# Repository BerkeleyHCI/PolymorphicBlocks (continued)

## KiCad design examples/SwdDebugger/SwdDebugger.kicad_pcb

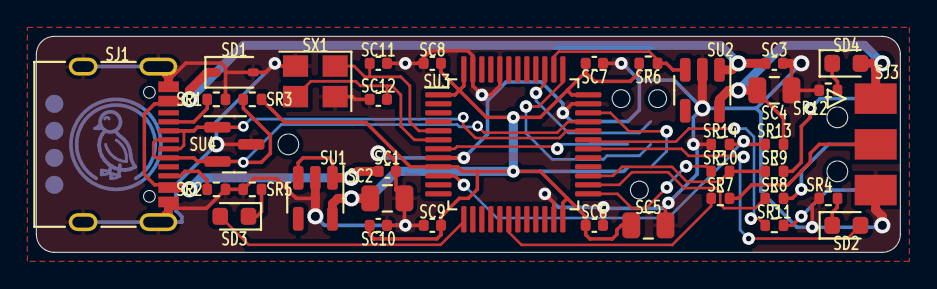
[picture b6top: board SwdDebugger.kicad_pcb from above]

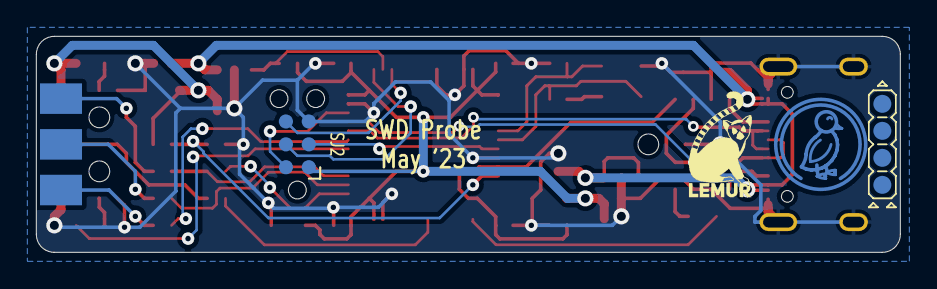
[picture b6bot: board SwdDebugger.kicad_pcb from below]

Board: 2 copper layers, 48.0 x 12.0 mm, 44 parts (4 on the bottom side), 30 nets.

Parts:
SC1, SC3, SC6, SC7, SC8, SC9, SC10, SC11, SC12: C_0402_1005Metric
SC2, SC4, SC5: C_0805_2012Metric
SD1: BZT52-B5V6S_R1_00001 (PANJIT International) - 100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; D_SOD-323
SD2, SD4: LED_0603_1608Metric
SD3: C2290 (Hubei KENTO Elec) - White 0603 Light Emitt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; LED_0603_1608Metric
SH1, SH2, SH3: JlcToolingHole_1.152mm
SJ1: COM-15111 (Sparkfun); USB_C_Receptacle_XKB_U262-16XN-4BVC11
SJ2: Tag-Connect_TC2030-IDC-NL_2x03_P1.27mm_Vertical
SJ3: PinHeader2.54 Shrouded 2x3 (Generic); PinHeader_2x03_P2.54mm_EdgeInline
SR1, SR2, SR3, SR4, SR5, SR6, SR7, SR8, SR9, SR10, SR11, SR12, SR13, SR14: R_0402_1005Metric
SU1, SU2: AP2204K-3.3 (Diodes Incorporated); SOT-23-5
SU3: STM32F103xxT6 (STMicroelectronics); LQFP-48_7x7mm_P0.5mm
SU4: PESD5V0X1BT (Nexperia); SOT-23
SX1: Crystal_SMD_3225-4Pin_3.2x2.5mm
UU4: Duck; Symbol_Duckling
UU5: Lemur; Symbol_LemurSmall
UU6: IdDots4; Indicator_IdDots_4

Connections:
en_pull.io: SR6.2, SU2.3, SU3.38
gnd: SC1.2, SC2.2, SC3.2, SC4.2, SC5.2, SC6.2, SC7.2, SC8.2, SC9.2, SC10.2, SC11.2, SC12.2, SD1.2, SJ1.A1, SJ1.A12, SJ1.B1, SJ1.B12, SJ1.S1, SJ2.5, SJ3.5, SR1.1, SR2.1, SR4.2, SR5.2, SR12.2, SR14.2, SU1.2, SU2.2, SU3.8, SU3.23, SU3.35, SU3.44, SU3.47, SU4.3, SX1.2, SX1.4
led_target.res.a: SD4.1, SR12.1
led_tgt.res.a: SD2.1, SR4.1
led_tgt.signal: SD2.2, SU3.30
led_usb.res.a: SD3.1, SR5.1
led_usb.signal: SD3.2, SU3.13
mcu.swd.swo: SJ2.6, SU3.39
mcu.swd_node.reset: SJ2.3, SU3.7
mcu.swd_node.swclk: SJ2.4, SU3.37
mcu.swd_node.swdio: SJ2.2, SU3.34
mcu.xtal_node.driver.xtal_in: SC11.1, SU3.5, SX1.1
mcu.xtal_node.driver.xtal_out: SC12.1, SU3.6, SX1.3
target_drv.reset_in: SR7.1, SU3.18
target_drv.swclk_in: SR8.1, SU3.26
target_drv.swd.reset: SJ3.3, SR7.2
target_drv.swd.swclk: SJ3.4, SR8.2
target_drv.swd.swdio: SJ3.2, SR9.2
target_drv.swdio_in: SR10.1, SU3.25
target_drv.swdio_out: SR9.1, SR10.2, SU3.27
target_drv.swo_in: SJ3.6, SR11.2
target_drv.swo_out: SR11.1, SU3.31
target_sense.output: SR13.2, SR14.1, SU3.10
usb.conn.A5: SJ1.A5, SR1.2
usb.conn.B5: SJ1.B5, SR2.2
usb_chain_0.d_N: SJ1.A7, SJ1.B7, SU3.32, SU4.1
usb_chain_0.d_P: SJ1.A6, SJ1.B6, SR3.2, SU3.33, SU4.2
v3v3: SC2.1, SC5.1, SC6.1, SC7.1, SC8.1, SC9.1, SC10.1, SJ2.1, SR3.1, SR6.1, SU1.5, SU3.1, SU3.9, SU3.24, SU3.36, SU3.48
vtarget: SC4.1, SD4.2, SJ3.1, SR13.1, SU2.5
vusb: SC1.1, SC3.1, SD1.1, SJ1.A4, SJ1.A9, SJ1.B4, SJ1.B9, SU1.1, SU1.3, SU2.1

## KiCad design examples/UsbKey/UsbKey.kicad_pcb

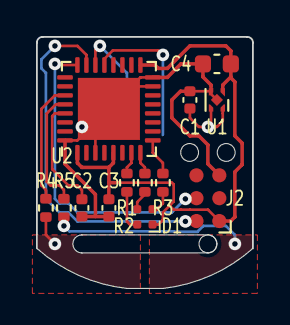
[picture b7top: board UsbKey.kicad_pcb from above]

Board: 2 copper layers, 12.0 x 14.0 mm, 14 parts (1 on the bottom side), 16 nets.

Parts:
C1, C2, C3: C_0402_1005Metric
C4: C_0603_1608Metric
D1: FC-B1010RGBT-HG (Foshan NationStar Optoelectronic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; LED_Lumex_SML-LX0404SIUPGUSB
J1: USB A pads; USB_A_Pads
J2: Tag-Connect_TC2030-IDC-NL_2x03_P1.27mm_Vertical
R1, R2, R3, R4, R5: R_0402_1005Metric
U1: LP5907SNX-3.3/NOPB (Texas Instruments); UDFN-4-1EP_1x1mm_P0.65mm_EP0.48x0.48mm
U2: STM32L432Kxxx (STMicroelectronics); QFN-32-1EP_5x5mm_P0.5mm_EP3.45x3.45mm

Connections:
gnd: C1.2, C2.2, C3.2, C4.2, J1.4, J2.5, U1.2, U1.5, U2.3, U2.15, U2.16, U2.32, U2.33
mcu.swd_node.swclk: J2.4, U2.24
mcu.swd_node.swdio: J2.2, U2.23
rgb.blue_res.a: D1.4, R3.1
rgb.green_res.a: D1.3, R2.1
rgb.red_res.a: D1.2, R1.1
rgb.signals.blue: R3.2, U2.9
rgb.signals.green: R2.2, U2.8
rgb.signals.red: R1.2, U2.7
ts1.io: R4.1, U2.27
ts2.io: R5.1, U2.28
tss.io: C2.1, U2.29
usb.pwr: C1.1, J1.1, U1.3, U1.4
usb.usb.dm: J1.2, U2.21
usb.usb.dp: J1.3, U2.22
v3v3: C3.1, C4.1, D1.1, J2.1, U1.1, U2.1, U2.5, U2.17

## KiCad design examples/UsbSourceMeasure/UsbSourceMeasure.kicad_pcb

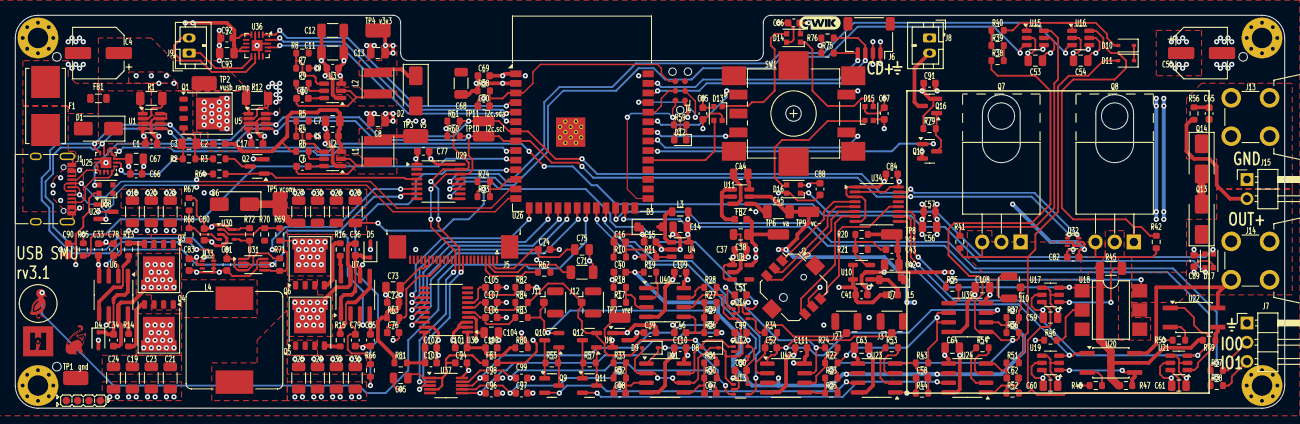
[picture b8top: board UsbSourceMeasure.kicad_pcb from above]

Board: 4 copper layers, 168.0 x 52.0 mm, 317 parts (0 on the bottom side), 176 nets.

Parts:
C1: vusb_sense.vs_cap; C_0603_1608Metric
C2: ramp.cap_gd; C_0603_1608Metric
C3: ramp.cap_gs; C_0805_2012Metric
C4: cap_conv; CP_Elec_6.3x7.7
C5: reg_v5.hf_in_cap; C_0603_1608Metric
C6: reg_v5.boot_cap; C_0603_1608Metric
C7: reg_v5.power_path.in_cap; C_0805_2012Metric
C8: reg_v5.power_path.out_cap; C_0805_2012Metric
C9: reg_3v3.hf_in_cap; C_0603_1608Metric
C10: reg_3v3.boot_cap; C_0603_1608Metric
C11: reg_3v3.power_path.in_cap.c[0]; C_1206_3216Metric
C12: reg_3v3.power_path.in_cap.c[1]; C_1206_3216Metric
C13: reg_3v3.power_path.out_cap; C_0805_2012Metric
C14: reg_v12.power_path.in_cap; C_0805_2012Metric
C15: reg_v12.power_path.out_cap; C_0603_1608Metric
C16: reg_v12.cf; C_0603_1608Metric
C17: convin_sense.vs_cap; C_0603_1608Metric
C18: conv.power_path.in_cap.c[0]; C_1206_3216Metric
C19: conv.power_path.in_cap.c[1]; C_1206_3216Metric
C20: conv.power_path.in_cap.c[2]; C_1206_3216Metric
C21: conv.power_path.in_cap.c[3]; C_1206_3216Metric
C22: conv.power_path.in_cap.c[4]; C_1206_3216Metric
C23: conv.power_path.in_cap.c[5]; C_1206_3216Metric
C24: conv.power_path.in_cap.c[6]; C_1206_3216Metric
C25: conv.power_path.out_cap.c[0]; C_1206_3216Metric
C26: conv.power_path.out_cap.c[1]; C_1206_3216Metric
C27: conv.power_path.out_cap.c[2]; C_1206_3216Metric
C28: conv.power_path.out_cap.c[3]; C_1206_3216Metric
C29: conv.power_path.out_cap.c[4]; C_1206_3216Metric
C30: conv.power_path.out_cap.c[5]; C_1206_3216Metric
C31: conv.power_path.out_cap.c[6]; C_1206_3216Metric
C32: conv.power_path.out_cap.c[7]; C_1206_3216Metric
C33: conv.buck_sw.driver.cap; C_0603_1608Metric
C34: conv.buck_sw.driver.high_cap; C_0603_1608Metric
C35: conv.boost_sw.driver.cap; C_0603_1608Metric
C36: conv.boost_sw.driver.high_cap; C_0603_1608Metric
C37: reg_analog.in_cap; C_0603_1608Metric
C38: reg_analog.out_cap; C_0805_2012Metric
C39: reg_vref.in_cap; C_0603_1608Metric
C40: ref_rc.c; C_0603_1608Metric
C41: reg_vcontrol.power_path.in_cap; C_0603_1608Metric
C42: reg_vcontrol.power_path.out_cap; C_0805_2012Metric
C43: reg_vcontrol.cf; C_0603_1608Metric
C44: reg_vcontroln.cf; C_0805_2012Metric
C45: reg_vcontroln.cout; C_1206_3216Metric
C46: control.err_volt.cin; C_0603_1608Metric
C47: control.err_source.cin; C_0603_1608Metric
C48: control.err_sink.cin; C_0603_1608Metric
C49: control.comp_source.vdd_cap; C_0603_1608Metric
C50: control.comp_sink.vdd_cap; C_0603_1608Metric
C51: control.off_sw.vdd_cap; C_0603_1608Metric
C52: control.int.c; C_0603_1608Metric
C53: control.driver.high_gate.vdd_cap; C_0805_2012Metric
C54: control.driver.low_gate.vdd_cap; C_0805_2012Metric
C55: control.driver.cap_in1; CP_Elec_6.3x7.7
C56: control.driver.cap_in2; C_0805_2012Metric
C57: control.driver.cap_in3; C_0603_1608Metric
C58: control.cdiv; C_0603_1608Metric
C59: control.isense.ranges[0].sense_sw.vdd_cap; C_0805_2012Metric
C60: control.isense.ranges[1].sense_sw.vdd_cap; C_0805_2012Metric
C61: control.isense.ranges[2].sense_sw.vdd_cap; C_0805_2012Metric
C62: control.ifilt.c; C_0603_1608Metric
C63: control.vmeas.vdd_cap; C_0805_2012Metric
C64: control.imeas.vdd_cap; C_0805_2012Metric
C65: control.snub_c; C_0603_1608Metric
C66: pd.vdd_cap[0]; C_0603_1608Metric
C67: pd.vdd_cap[1]; C_0805_2012Metric
C68: mcu.vcc_cap0; C_1206_3216Metric
C69: mcu.vcc_cap1; C_0603_1608Metric
C70: mcu.en_pull.c; C_0603_1608Metric
C71: oled.vcomh_cap; C_1206_3216Metric
C72: oled.vdd_cap1; C_0603_1608Metric
C73: oled.vdd_cap2; C_0805_2012Metric
C74: oled.vcc_cap1; C_0603_1608Metric
C75: oled.vcc_cap2; C_0805_2012Metric
C76: oled_rc.c; C_0603_1608Metric
C77: ioe_ctl.vdd_cap; C_0603_1608Metric
C78: buck_rc.c; C_0603_1608Metric
C79: boost_rc.c; C_0603_1608Metric
C80: conv_ovp.comp.vdd_cap; C_0603_1608Metric
C81: conv_latch.vdd_cap; C_0603_1608Metric
C82: pass_temp.vdd_cap; C_0603_1608Metric
C83: conv_temp.vdd_cap; C_0603_1608Metric
C84: ioe_ui.vdd_cap; C_0603_1608Metric
C85: rgbs.led[0].cap; C_0603_1608Metric
C86: rgbs.led[1].cap; C_0603_1608Metric
C87: rgbs.led[2].cap; C_0603_1608Metric
C88: rgbs.led[3].cap; C_0603_1608Metric
C89: rgbs.led[4].cap; C_0603_1608Metric
C90: rgbs.led[5].cap; C_0603_1608Metric
C91: fan_cap; C_0603_1608Metric
C92: spk_drv.pwr_cap0; C_0603_1608Metric
C93: spk_drv.pwr_cap1; C_0805_2012Metric
C94: dac.vdd_cap[0]; C_0603_1608Metric
C95: dac.vdd_cap[1]; C_0805_2012Metric
C96: dac.out_cap[0]; C_0603_1608Metric
C97: dac.out_cap[1]; C_0603_1608Metric
C98: dac.out_cap[2]; C_0603_1608Metric
C99: dac.out_cap[3]; C_0603_1608Metric
C100: adc.avdd_cap_0; C_0603_1608Metric
C101: adc.avdd_cap_1; C_0603_1608Metric
C102: adc.dvdd_cap_0; C_0603_1608Metric
C103: adc.dvdd_cap_1; C_0603_1608Metric
C104: adc.vref_cap; C_0805_2012Metric
C105: vcen_rc.c; C_0603_1608Metric
C106: mv_rc.c; C_0603_1608Metric
C107: mi_rc.c; C_0603_1608Metric
C108: vimeas_amps.vdd_cap; C_0805_2012Metric
C109: cv_amps.vdd_cap; C_0603_1608Metric
C110: ci_amps.vdd_cap; C_0603_1608Metric
C111: cintref_amps.vdd_cap; C_0603_1608Metric
D1: prot_vusb; D_SMA
D2: prot_3v3; D_SMA
D3: reg_v12.rect; D_SOD-123
D4: conv.buck_sw.driver.boot; D_SOD-323
D5: conv.boost_sw.driver.boot; D_SOD-323
D6: prot_conv; D_SMA
D7: reg_vcontrol.rect; D_SOD-123
D8: control.err_source.diode; D_SOD-323
D9: control.err_sink.diode; D_SOD-323
D10: control.driver.clamp1; D_SOD-323
D11: control.driver.clamp2; D_SOD-323
D12: led.package; LED_0603_1608Metric
D13: rgbs.led[0].device; LED_WS2812B-2020_PLCC4_2.0x2.0mm
D14: rgbs.led[1].device; LED_WS2812B-2020_PLCC4_2.0x2.0mm
D15: rgbs.led[2].device; LED_WS2812B-2020_PLCC4_2.0x2.0mm
D16: rgbs.led[3].device; LED_WS2812B-2020_PLCC4_2.0x2.0mm
D17: rgbs.led[4].device; LED_WS2812B-2020_PLCC4_2.0x2.0mm
D18: rgbs.led[5].device; LED_WS2812B-2020_PLCC4_2.0x2.0mm
F1: fuse_vusb; Fuseholder_Littelfuse_Nano2_154x
FB1: filt_vusb; L_0805_2012Metric
FB2: filt_vcontroln; L_0603_1608Metric
FB3: dac_ferrite; L_0603_1608Metric
H1: jlc_th.th1; JlcToolingHole_1.152mm
H2: jlc_th.th2; JlcToolingHole_1.152mm
H3: jlc_th.th3; JlcToolingHole_1.152mm
J1: usb; USB_C_Receptacle_XKB_U262-16XN-4BVC11
J2: tp_err; U.FL_Hirose_U.FL-R-SMT-1_Vertical
J3: tp_int; U.FL_Hirose_U.FL-R-SMT-1_Vertical
J4: mcu.prog; Tag-Connect_TC2030-IDC-NL_2x03_P1.27mm_Vertical
J5: oled.device; TE_2-1734839-4_1x24-1MP_P0.5mm_Horizontal
J6: qwiic; JST_SH_SM04B-SRSS-TB_1x04-1MP_P1.00mm_Horizontal
J7: dutio; PinHeader_1x03_P2.54mm_Horizontal
J8: fan; JST_PH_B2B-PH-K_1x02_P2.00mm_Vertical
J9: spk; JST_PH_B2B-PH-K_1x02_P2.00mm_Vertical
J10: tp_vcen; U.FL_Hirose_U.FL-R-SMT-1_Vertical
J11: tp_mv; U.FL_Hirose_U.FL-R-SMT-1_Vertical
J12: tp_mi; U.FL_Hirose_U.FL-R-SMT-1_Vertical
J13: outn; CalTest_CT3151
J14: outp; CalTest_CT3151
J15: outd; PinHeader_1x02_P2.54mm_Horizontal
L1: reg_v5.power_path.inductor; L_Taiyo-Yuden_NR-40xx
L2: reg_3v3.power_path.inductor; L_Taiyo-Yuden_NR-40xx
L3: reg_v12.power_path.inductor; L_0805_2012Metric
L4: conv.power_path.inductor; L_Bourns_SRP1245A
L5: reg_vcontrol.power_path.inductor; L_0603_1608Metric
MH1, MH2, MH3, MH4: MountingHole_2.7mm_M2.5_Pad_Via
Q1: ramp.drv; PQFN-8-EP_6x5mm_P1.27mm_Generic
Q2: ramp.ctl_fet; SOT-23
Q3: conv.buck_sw.low_fet; PQFN-8-EP_6x5mm_P1.27mm_Generic
Q4: conv.buck_sw.high_fet; PQFN-8-EP_6x5mm_P1.27mm_Generic
Q5: conv.boost_sw.low_fet; PQFN-8-EP_6x5mm_P1.27mm_Generic
Q6: conv.boost_sw.high_fet; PQFN-8-EP_6x5mm_P1.27mm_Generic
Q7: control.driver.high_fet; TO-220-3_Horizontal_TabUp
Q8: control.driver.low_fet; TO-220-3_Horizontal_TabUp
Q9: control.vclamp.Q1; SOT-23
Q10: control.vclamp.Q2; SOT-23
Q11: control.iclamp.Q1; SOT-23
Q12: control.iclamp.Q2; SOT-23
Q13: control.Q1; D_SMA
Q14: control.Q2; D_SMA
Q15: fan_drv.pre; SOT-23
Q16: fan_drv.drv; SOT-23
R1: vusb_sense.Rs; R_1206_3216Metric
R2: ramp.div.top_res; R_0603_1608Metric
R3: ramp.div.bottom_res; R_0603_1608Metric
R4: reg_v5.fb.top_res; R_0603_1608Metric
R5: reg_v5.fb.bottom_res; R_0603_1608Metric
R6: reg_v5.en_res; R_0603_1608Metric
R7: reg_3v3.fb.top_res; R_0603_1608Metric
R8: reg_3v3.fb.bottom_res; R_0603_1608Metric
R9: reg_3v3.en_res; R_0603_1608Metric
R10: reg_v12.fb.top_res; R_0603_1608Metric
R11: reg_v12.fb.bottom_res; R_0603_1608Metric
R12: convin_sense.Rs; R_1206_3216Metric
R13: conv.buck_sw.low_gate_res; R_0603_1608Metric
R14: conv.buck_sw.high_gate_res; R_0603_1608Metric
R15: conv.boost_sw.low_gate_res; R_0603_1608Metric
R16: conv.boost_sw.high_gate_res; R_0603_1608Metric
R17: ref_div.top_res; R_0603_1608Metric
R18: ref_div.bottom_res; R_0603_1608Metric
R19: ref_rc.r; R_0603_1608Metric
R20: reg_vcontrol.fb.top_res; R_0603_1608Metric
R21: reg_vcontrol.fb.bottom_res; R_0603_1608Metric
R22: control.dmeas.r1; R_0603_1608Metric
R23: control.dmeas.r2; R_0603_1608Metric
R24: control.dmeas.rf; R_0603_1608Metric
R25: control.dmeas.rg; R_0603_1608Metric
R26: control.err_volt.rtop; R_0603_1608Metric
R27: control.err_volt.rbot; R_0603_1608Metric
R28: control.err_volt.rout; R_0603_1608Metric
R29: control.err_volt.rfine; R_0603_1608Metric
R30: control.err_source.rtop; R_0603_1608Metric
R31: control.err_source.rbot; R_0603_1608Metric
R32: control.err_sink.rtop; R_0603_1608Metric
R33: control.err_sink.rbot; R_0603_1608Metric
R34: control.int.r; R_0603_1608Metric
R35: control.hvclamp; R_0603_1608Metric
R36: control.amp.r1; R_0603_1608Metric
R37: control.amp.r2; R_0603_1608Metric
R38: control.driver.res.res[0]; R_0603_1608Metric
R39: control.driver.res.res[1]; R_0603_1608Metric
R40: control.driver.res.res[2]; R_0603_1608Metric
R41: control.driver.high_res; R_0603_1608Metric
R42: control.driver.low_res; R_0603_1608Metric
R43: control.vdiv.top_res; R_0603_1608Metric
R44: control.vdiv.bottom_res; R_0603_1608Metric
R45: control.isense.ranges[0].isense; R_1206_3216Metric
R46: control.isense.ranges[0].pwr_sw.res; R_0603_1608Metric
R47: control.isense.ranges[1].isense; R_0603_1608Metric
R48: control.isense.ranges[1].pwr_sw.res; R_0603_1608Metric
R49: control.isense.ranges[2].isense; R_0603_1608Metric
R50: control.isense.ranges[2].pwr_sw.res; R_0603_1608Metric
R51: control.ifilt.rp; R_0603_1608Metric
R52: control.ifilt.rn; R_0603_1608Metric
R53: control.vmeas.rg; R_0603_1608Metric
R54: control.imeas.rg; R_0603_1608Metric
R55: control.vclamp.r; R_0603_1608Metric
R56: control.snub_r; R_0603_1608Metric
R57: control.iclamp.r; R_0603_1608Metric
R58: mcu.en_pull.r; R_0603_1608Metric
R59: led.res; R_0603_1608Metric
R60: i2c_pull.scl_res; R_0603_1608Metric
R61: i2c_pull.sda_res; R_0603_1608Metric
R62: oled.iref_res; R_0603_1608Metric
R63: oled_rc.r; R_0603_1608Metric
R64: ramp_pull; R_0603_1608Metric
R65: buck_rc.r; R_0603_1608Metric
R66: boost_rc.r; R_0603_1608Metric
R67: conv_ovp.ref_div.top_res; R_0603_1608Metric
R68: conv_ovp.ref_div.bottom_res; R_0603_1608Metric
R69: conv_ovp.comp_div.top_res; R_0603_1608Metric
R70: conv_ovp.comp_div.bottom_res; R_0603_1608Metric
R71: conv_en_pull; R_0603_1608Metric
R72: comp_pull; R_0603_1608Metric
R73: conv_sense.top_res; R_0603_1608Metric
R74: conv_sense.bottom_res; R_0603_1608Metric
R75: qwiic_pull.scl_res; R_0603_1608Metric
R76: qwiic_pull.sda_res; R_0603_1608Metric
R77: dut0_clamp; R_0603_1608Metric
R78: dut1_clamp; R_0603_1608Metric
R79: fan_drv.pull; R_0603_1608Metric
R80: adc.avdd_res; R_0603_1608Metric
R81: adc.dvdd_res; R_0603_1608Metric
R82: vcen_rc.r; R_0603_1608Metric
R83: mv_rc.r; R_0603_1608Metric
R84: mi_rc.r; R_0603_1608Metric
SW1: enc; RotaryEncoder_Bourns_PEC11S
SW2: dir; DirectionSwitch_Alps_SKRH
SYM1: G***; Symbol_LemurSolid
SYM2: G***; Symbol_HiLabSolid
TP1: gnd; TestPoint_TE_RCT_0805
TP2: vusb_ramp; TestPoint_TE_RCT_0805
TP3: v5; TestPoint_TE_RCT_0805
TP4: v3v3; TestPoint_TE_RCT_0805
TP5: vconv; TestPoint_TE_RCT_0805
TP6: va; TestPoint_TE_RCT_0805
TP7: vref; TestPoint_TE_RCT_0805
TP8: vc+; TestPoint_TE_RCT_0805
TP9: vc-; TestPoint_TE_RCT_0805
TP10: i2c.scl; TestPoint_TE_RCT_0805
TP11: i2c.sda; TestPoint_TE_RCT_0805
U1: vusb_sense.ic; SOT-23-8
U2: reg_v5.ic; SOT-23-6
U3: reg_3v3.ic; SOT-23-6
U4: reg_v12.ic; SOT-23-5
U5: convin_sense.ic; SOT-23-8
U6: conv.buck_sw.driver.ic; SOIC-8_3.9x4.9mm_P1.27mm
U7: conv.boost_sw.driver.ic; SOIC-8_3.9x4.9mm_P1.27mm
U8: reg_analog.ic; SOT-23-5
U9: reg_vref.ic; SOT-23
U10: reg_vcontrol.ic; SOT-23-5
U11: reg_vcontroln.ic; SOT-23-6
U12: control.comp_source.ic; SOT-353_SC-70-5
U13: control.comp_sink.ic; SOT-353_SC-70-5
U14: control.off_sw.ic; SOT-363_SC-70-6
U15: control.driver.high_gate.ic; SOT-23-6
U16: control.driver.low_gate.ic; SOT-23-6
U17: control.isense.ranges[0].sense_sw.ic; SOT-23-6
U18: control.isense.ranges[0].pwr_sw.ic; SMDIP-6_W7.62mm
U19: control.isense.ranges[1].sense_sw.ic; SOT-23-6
U20: control.isense.ranges[1].pwr_sw.ic; SO-4_4.4x3.6mm_P2.54mm
U21: control.isense.ranges[2].sense_sw.ic; SOT-23-6
U22: control.isense.ranges[2].pwr_sw.ic; SO-4_4.4x3.6mm_P2.54mm
U23: control.vmeas.ic; SOIC-8_3.9x4.9mm_P1.27mm
U24: control.imeas.ic; SOIC-8_3.9x4.9mm_P1.27mm
U25: pd.ic; WQFN-14-1EP_2.5x2.5mm_P0.5mm_EP1.45x1.45mm
U26: mcu.ic; ESP32-S3-WROOM-1
U27: usb_esd; SOT-23
U28: oled.lcd; Lcd_Er_Oled022_1_Outline
U29: ioe_ctl.ic; TSSOP-16_4.4x5mm_P0.65mm
U30: conv_ovp.comp.ic; SOT-353_SC-70-5
U31: conv_latch.ic; VSSOP-8_2.3x2mm_P0.5mm
U32: pass_temp.ic; SOT-563
U33: conv_temp.ic; SOT-563
U34: ioe_ui.ic; TSSOP-16_4.4x5mm_P0.65mm
U35: touch_duck; Symbol_DucklingSolid
U36: spk_drv.ic; QFN-16-1EP_3x3mm_P0.5mm_EP1.45x1.45mm
U37: dac.ic; MSOP-10_3x3mm_P0.5mm
U38: adc.ic; TSSOP-20_4.4x6.5mm_P0.65mm
U39: vimeas_amps.ic; SOIC-8_3.9x4.9mm_P1.27mm
U40: cv_amps.ic; SOIC-8_3.9x4.9mm_P1.27mm
U41: ci_amps.ic; SOIC-8_3.9x4.9mm_P1.27mm
U42: cintref_amps.ic; SOIC-8_3.9x4.9mm_P1.27mm

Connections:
adc.cs: U26.15, U38.13
adc.ic.avdd: C100.1, C101.1, R80.2, U38.1
adc.ic.dvdd: C102.1, C103.1, R81.2, U38.20
adc.mclkin: U26.20, U38.18
adc.spi.miso: U26.19, U38.16
adc.spi.mosi: U26.18, U38.15
adc.spi.sck: U26.17, U38.14
boost_rc.input: R66.1, U26.11
boost_rc.output: C79.1, R66.2, U7.2
buck_rc.input: R65.1, U26.10
buck_rc.output: C78.1, R65.2, U6.2
ci_amps.inp.0: C48.1, R32.2, R33.2, U41.3
ci_amps.inp.1: C47.1, R30.2, R31.2, U41.5
ci_amps.out.0: D9.1, U13.3, U41.1
ci_amps.out.1: D8.2, U12.1, U41.7
cintref_amps.inn.0: C52.2, R34.2, U42.2
cintref_amps.inn.1: R22.2, R24.2, U42.6
cintref_amps.inp.1: R23.2, R25.2, U42.5
cintref_amps.out.1: R24.1, U14.1, U42.7
control.Q1.ports.2: Q13.2, Q14.2
control.drive: R23.1, R36.1, R38.1, U39.1
control.driver.clamp1.cathode: D10.1, D11.1
control.driver.high_fet.gate: Q7.1, R41.1, U15.6
control.driver.low_fet.gate: Q8.1, R42.1, U16.6
control.driver.out: D11.2, Q7.3, Q8.3, R41.2, R42.2, R45.1, R47.1, R49.1, R51.1
control.driver.res.b: D10.2, R40.2, U15.1, U16.1
control.driver.res.res[0].b: R38.2, R39.1
control.driver.res.res[1].b: R39.2, R40.1
control.high_gate_ctl: U15.3, U29.11
control.iclamp.r.a: Q11.1, Q12.3, R57.1
control.iclamp.r.b: Q11.3, Q12.1, R57.2
control.ifilt.outn: C62.2, R52.2, U24.1
control.ifilt.outp: C62.1, R51.2, U24.4
control.imeas.output: Q11.2, U24.7
control.imeas.rg.a: R54.1, U24.2
control.imeas.rg.b: R54.2, U24.3
control.int_link: J2.1, R34.1, U14.4
control.isense.ranges[0].isense.pwr_out: R45.2, U17.1, U18.4
control.isense.ranges[0].pwr_sw.res.a: R46.1, U18.2
control.isense.ranges[1].isense.pwr_out: R47.2, U19.1, U20.3
control.isense.ranges[1].pwr_sw.res.a: R48.1, U20.2
control.isense.ranges[2].isense.pwr_out: R49.2, U21.1, U22.3
control.isense.ranges[2].pwr_sw.res.a: R50.1, U22.2
control.isense.sense_out: R52.1, U17.6, U19.6, U21.6
control.limit_sink: U13.4, U26.23
control.limit_source: U12.4, U26.22
control.low_gate_ctl: U16.3, U29.12
control.meas_i: J12.1, Q12.2, R31.1, R33.1, R84.1
control.meas_v: J11.1, Q10.2, R27.1, R83.1
control.outa: R22.1, R43.1, U39.6, U39.7
control.snub_r.pwr_out: C65.1, R56.2
control.tp_int: C52.1, J3.1, U39.3, U42.1
control.vclamp.r.a: Q9.1, Q10.3, R55.1
control.vclamp.r.b: Q9.3, Q10.1, R55.2
control.vdiv.output: C58.1, R43.2, R44.1, U23.4
control.vmeas.output: Q9.2, U23.7
control.vmeas.rg.a: R53.1, U23.2
control.vmeas.rg.b: R53.2, U23.3
conv.boost_sw.driver.ic.bst: C36.1, D5.1, U7.1
conv.boost_sw.high_gate_res.a: R16.1, U7.8
conv.boost_sw.high_gate_res.b: Q6.4, R16.2
conv.boost_sw.low_gate_res.a: R15.1, U7.5
conv.boost_sw.low_gate_res.b: Q5.4, R15.2
conv.buck_sw.driver.ic.bst: C34.1, D4.1, U6.1
conv.buck_sw.high_gate_res.a: R14.1, U6.8
conv.buck_sw.high_gate_res.b: Q4.4, R14.2
conv.buck_sw.low_gate_res.a: R13.1, U6.5
conv.buck_sw.low_gate_res.b: Q3.4, R13.2
conv.l1: C34.2, L4.1, Q3.5, Q4.1, Q4.2, Q4.3, U6.7
conv.l2: C36.2, L4.2, Q5.5, Q6.1, Q6.2, Q6.3, U7.7
conv_en_pull.io: R71.2, U29.6, U31.5
conv_latch.ic.out2: U31.2, U31.3
conv_latch.out: U6.3, U7.3, U29.7, U31.6, U31.7
conv_ovp.comp.inn: R67.2, R68.1, U30.3
conv_ovp.comp.inp: R69.2, R70.1, U30.1
conv_ovp.output: R72.2, U30.4, U31.1
conv_sense.output: R73.2, R74.1, U26.12
cv_amps.inn.1: D8.1, D9.2, R28.2, U12.3, U13.1, U14.3, U40.6, U41.2, U41.6
cv_amps.inp.1: C46.1, R26.2, R27.2, R29.2, U40.5
cv_amps.out.1: R28.1, U40.7
dac.out0: C96.1, R26.1, U37.6
dac.out1: C97.1, R32.1, U37.7
dac.out2: C98.1, R29.1, U37.8
dac.out3: C99.1, R30.1, U37.9
dac_ferrite.pwr_out: C94.1, C95.1, FB3.2, U37.1, U37.4
dir.a: SW2.1, U34.4
dir.b: SW2.4, U34.12
dir.c: SW2.3, U34.6
dir.center: SW2.2, U34.5
dir.d: SW2.6, U34.7
dut0_clamp.signal_out: R77.2, U26.24
dut1_clamp.signal_out: R78.2, U26.25
dutio.io0: J7.2, R77.1
dutio.io1: J7.3, R78.1
enc.a: SW1.A, U26.35
enc.b: SW1.B, U26.34
enc.sw: SW1.S1, U26.33
fan.pwr: J8.2, Q16.3
fan_drv.control: Q15.1, U26.32
fan_drv.pre.drain: Q15.3, Q16.1, R79.2
filt_vcontroln.pwr_out: FB2.2, U11.4, U11.5
filt_vusb.pwr_out: D1.1, FB1.2, R1.1, U1.1
fuse_vusb.pwr_out: F1.2, FB1.1
gnd: C1.2, C4.2, C5.2, C7.2, C8.2, C9.2, C11.2, C12.2, C13.2, C14.2, C15.2, C17.2, C18.2, C19.2, C20.2, C21.2, C22.2, C23.2, C24.2, C25.2, C26.2, C27.2, C28.2, C29.2, C30.2, C31.2, C32.2, C33.2, C35.2, C37.2, C38.2, C39.2, C40.2, C41.2, C42.2, C45.2, C46.2, C47.2, C48.2, C49.2, C50.2, C51.2, C55.2, C56.2, C57.2, C58.2, C59.2, C60.2, C61.2, C65.2, C66.2, C67.2, C68.2, C69.2, C70.2, C71.2, C72.2, C73.2, C74.2, C75.2, C76.2, C77.2, C78.2, C79.2, C80.2, C81.2, C82.2, C83.2, C84.2, C85.2, C86.2, C87.2, C88.2, C89.2, C90.2, C91.2, C92.2, C93.2, C94.2, C95.2, C96.2, C97.2, C98.2, C99.2, C100.2, C101.2, C102.2, C103.2, C104.2, C105.2, C106.2, C107.2, C109.2, C110.2, C111.2, D1.2, D2.2, D6.2, D13.2, D14.2, D15.2, D16.2, D17.2, D18.2, J1.A1, J1.A12, J1.B1, J1.B12, J1.S1, J2.2, J3.2, J4.5, J5.1, J5.5, J5.6, J5.7, J5.8, J5.9, J5.13, J5.14, J5.15, J5.17, J5.18, J5.22, J5.23, J5.24, J6.1, J7.1, J8.1, J10.2, J11.2, J12.2, J13.1, J15.1, Q2.2, Q3.1, Q3.2, Q3.3, Q5.1, Q5.2, Q5.3, Q8.2, Q14.1, Q15.2, R5.2, R8.2, R11.2, R18.2, R21.2, R44.2, R46.2, R48.2, R50.2, R62.2, R64.1, R68.2, R70.2, R71.1, R74.2, SW1.C, SW1.S2, SW2.5, TP1.1, U1.3, U1.7, U1.8, U2.1, U3.1, U4.2, U5.3, U5.7, U6.6, U7.6, U8.2, U9.3, U10.2, U11.1, U12.2, U13.2, U14.2, U15.4, U16.4, U17.2, U17.4, U19.2, U19.4, U21.2, U21.4, U23.1, U25.8, U25.9, U25.15, U26.1, U26.40, U26.41, U27.3, U29.1, U29.2, U29.3, U29.8, U30.2, U31.4, U32.2, U32.4, U33.2, U34.1, U34.3, U34.8, U36.3, U36.11, U36.15, U36.17, U37.10, U38.2, U38.3, U38.19, U40.4, U41.4, U42.4
i2c_pull.i2c.scl: J5.12, R60.2, TP10.1, U1.5, U5.5, U25.6, U26.8, U29.14, U32.1, U33.1, U34.14, U37.2
i2c_pull.i2c.sda: J5.10, J5.11, R61.2, TP11.1, U1.6, U5.6, U25.7, U26.7, U29.15, U32.6, U33.6, U34.15, U37.3
ioe_ctl.io.off_0: U14.6, U29.9
ioe_ui.io.irange_0: U17.3, U18.1, U34.11
ioe_ui.io.irange_1: U19.3, U20.1, U34.9
ioe_ui.io.irange_2: U21.3, U22.1, U34.10
led.res.a: D12.1, R59.1
mcu.program_boot_node: J4.2, R59.2, U26.27
mcu.program_en_node: C70.1, J4.6, R58.2, U26.3
mcu.program_uart_node.a_tx: J4.3, U26.37
mcu.program_uart_node.b_tx: J4.4, U26.36
mi_rc.output: C107.1, R84.2, U38.6
mv_rc.output: C106.1, R83.2, U38.5
oled.device.vcomh: C71.1, J5.3
oled.iref_res.a: J5.4, R62.1
oled.reset: C76.1, J5.16, R63.2
outp.port: J14.1, J15.2, Q13.1, R35.1, R56.1, U18.6, U20.4, U22.4
pd.ic.vconn: U25.12, U25.13
pd.int: U25.5, U26.9
qwiic_pull.i2c.scl: J6.4, R75.2, U26.39
qwiic_pull.i2c.sda: J6.3, R76.2, U26.38
ramp.ctl_fet.drain: Q2.3, R3.2
ramp.div.center: C2.2, C3.2, Q1.4, R2.2, R3.1
ramp_pull.io: Q2.1, R64.2, U29.4
ref_buf.output: R19.1, U40.1, U40.2
ref_div.output: R17.2, R18.1, U40.3
reg_3v3.boot_cap.neg: C10.2, L2.1, U3.2
reg_3v3.boot_cap.pos: C10.1, U3.6
reg_3v3.en_res.b: R9.2, U3.5
reg_3v3.fb.output: R7.2, R8.1, U3.4
reg_v5.boot_cap.neg: C6.2, L1.1, U2.2
reg_v5.boot_cap.pos: C6.1, U2.6
reg_v5.en_res.b: R6.2, U2.5
reg_v5.fb.output: R4.2, R5.1, U2.4
reg_v12.fb.output: C16.2, R10.2, R11.1, U4.3
reg_v12.power_path.switch: D3.2, L3.2, U4.1
reg_vcontrol.fb.output: C43.2, R20.2, R21.1, U10.3
reg_vcontrol.power_path.switch: D7.2, L5.2, U10.1
reg_vcontroln.cf.neg: C44.2, U11.3
reg_vcontroln.cf.pos: C44.1, U11.6
rgbs.din: D13.3, U26.31
rgbs.led[0].dout: D13.1, D14.3
rgbs.led[1].dout: D14.1, D15.3
rgbs.led[2].dout: D15.1, D16.3
rgbs.led[3].dout: D16.1, D17.3
rgbs.led[4].dout: D17.1, D18.3
spk_drv.i2s.sck: U26.5, U36.16
spk_drv.i2s.sd: U26.4, U36.1
spk_drv.i2s.ws: U26.6, U36.14
spk_drv.out.a: J9.1, U36.9
spk_drv.out.b: J9.2, U36.10
touch_duck.pad: U26.21, U35.1
usb.cc.cc1: J1.A5, U25.10, U25.11
usb.cc.cc2: J1.B5, U25.1, U25.14
usb.pwr: F1.1, J1.A4, J1.A9, J1.B4, J1.B9
usb_chain_0.d_N: J1.A7, J1.B7, U26.13, U27.1
usb_chain_0.d_P: J1.A6, J1.B6, U26.14, U27.2
v3v3: C1.1, C13.1, C17.1, C66.1, C67.1, C68.1, C69.1, C72.1, C73.1, C77.1, C80.1, C81.1, C82.1, C83.1, C84.1, D2.1, D12.2, J4.1, J5.19, J5.20, J6.2, L2.2, R7.1, R58.1, R60.1, R61.1, R63.1, R67.1, R72.1, R75.1, R76.1, R81.1, TP4.1, U1.4, U5.4, U5.8, U25.3, U25.4, U26.2, U29.16, U30.5, U31.8, U32.5, U33.4, U33.5, U34.2, U34.16
v5: C8.1, C14.1, C33.1, C35.1, C37.1, C39.1, C41.1, C85.1, C86.1, C87.1, C88.1, C89.1, C90.1, C91.1, C92.1, C93.1, D4.2, D5.2, D13.4, D14.4, D15.4, D16.4, D17.4, D18.4, L1.2, L3.1, L5.1, Q16.2, R4.1, R79.1, TP3.1, U4.4, U4.5, U6.4, U7.4, U8.1, U8.3, U9.1, U10.4, U10.5, U36.4, U36.7, U36.8
v12: C15.1, C16.1, C74.1, C75.1, D3.1, J5.2, R10.1
vanalog: C38.1, C49.1, C50.1, C51.1, C109.1, C110.1, C111.1, FB2.1, R80.1, TP6.1, U8.5, U12.5, U13.5, U14.5, U40.8, U41.8, U42.8
vcen_rc.output: C105.1, R82.2, U38.7
vcenter: C40.1, J10.1, R19.2, R25.1, R37.2, R82.1, U23.6, U24.6, U42.3
vcontrol: C42.1, C43.1, C53.1, C54.1, C59.1, C60.1, C61.1, C63.1, C64.1, C108.1, D7.1, R20.1, TP8.1, U15.5, U16.5, U17.5, U19.5, U21.5, U23.8, U24.8, U39.8
vcontroln: C45.1, C53.2, C54.2, C63.2, C64.2, C108.2, TP9.1, U11.2, U15.2, U16.2, U23.5, U24.5, U39.4
vconv: C25.1, C26.1, C27.1, C28.1, C29.1, C30.1, C31.1, C32.1, C55.1, C56.1, C57.1, D6.1, Q6.5, Q7.2, R69.1, R73.1, TP5.1
vconvin: C18.1, C19.1, C20.1, C21.1, C22.1, C23.1, C24.1, Q4.5, R12.2, U5.2
vimeas_amps.inn.0: R36.2, R37.1, U39.2
vimeas_amps.inp.1: R35.2, U39.5
vref: C104.1, FB3.1, R17.1, TP7.1, U9.2, U38.4
vusb: C3.1, C9.1, C11.1, C12.1, Q1.1, Q1.2, Q1.3, R1.2, R2.1, R9.1, U1.2, U3.3, U25.2
vusb_ramp: C2.1, C4.1, C5.1, C7.1, Q1.5, R6.1, R12.1, TP2.1, U2.3, U5.1
